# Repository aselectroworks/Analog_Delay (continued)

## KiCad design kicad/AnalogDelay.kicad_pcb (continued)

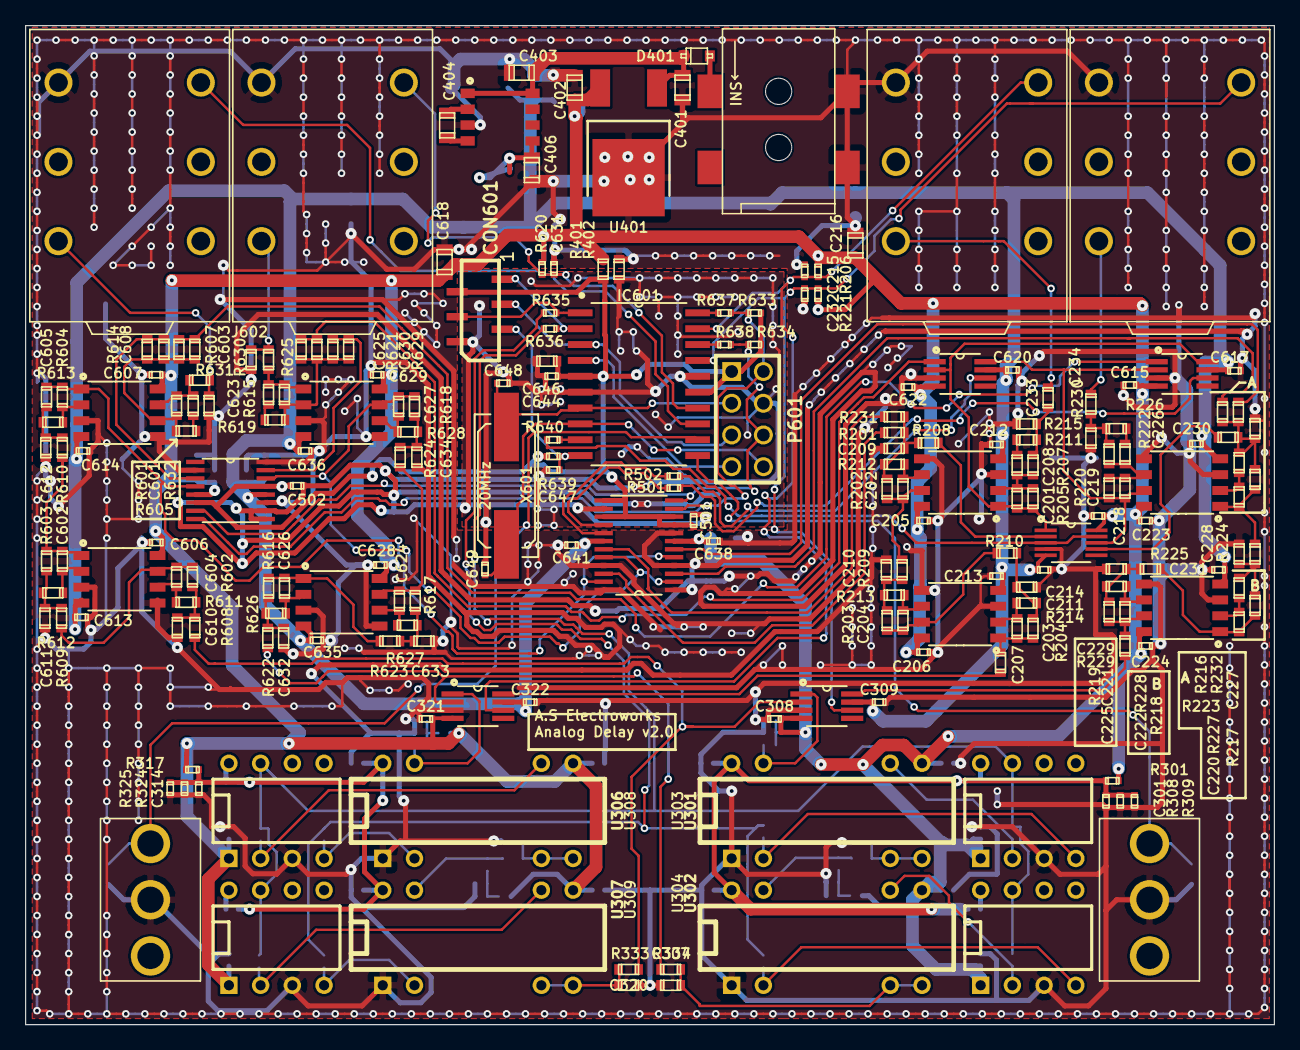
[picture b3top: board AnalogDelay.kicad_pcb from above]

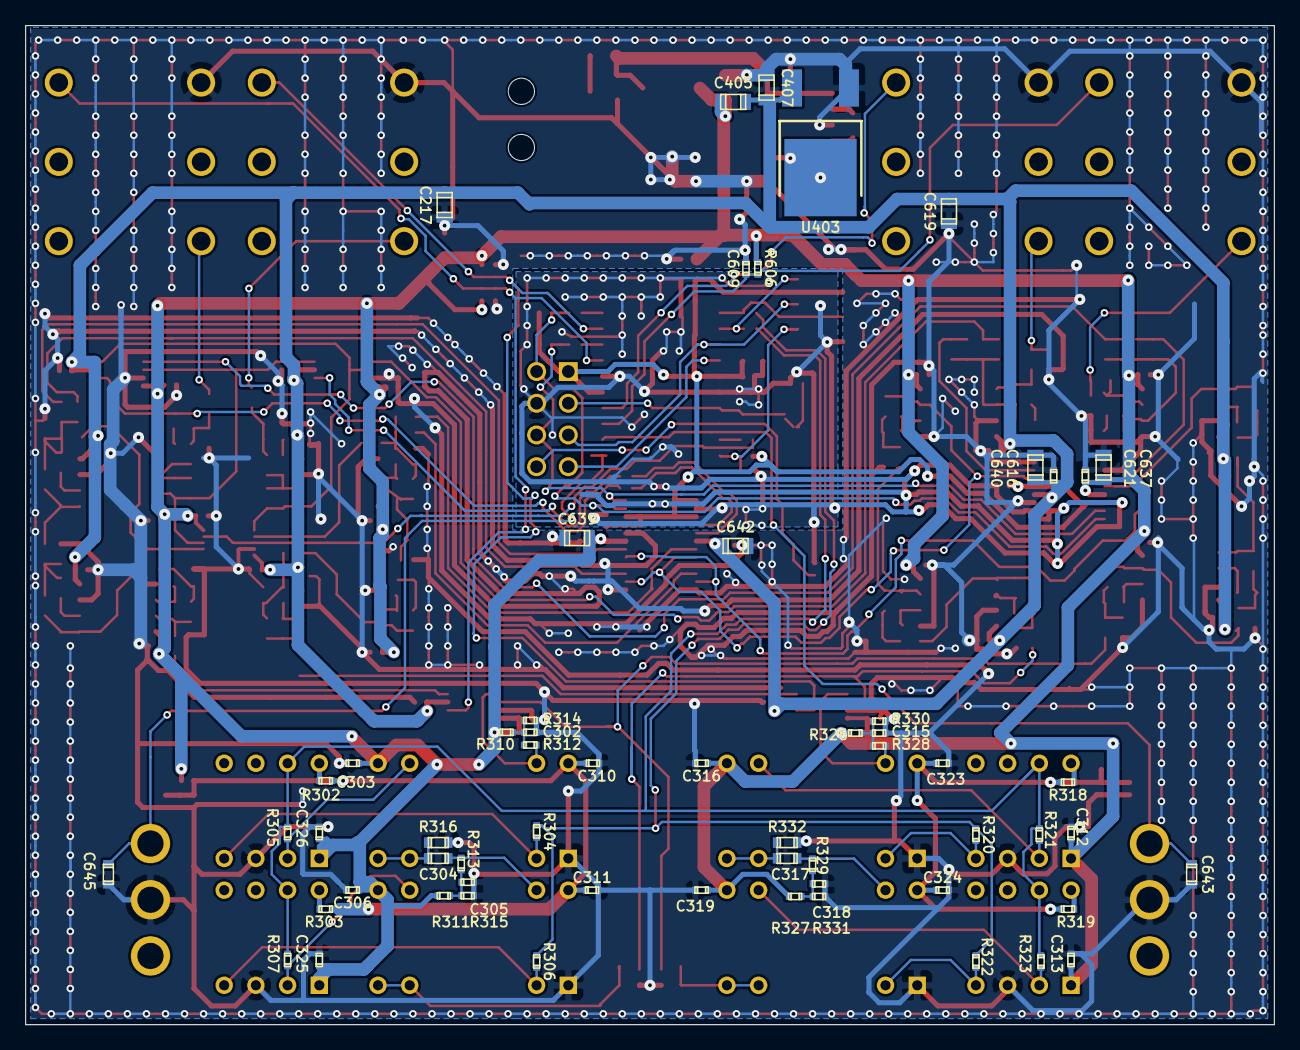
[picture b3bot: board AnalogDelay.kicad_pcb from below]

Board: 4 copper layers, 100.0 x 80.0 mm, 266 parts (59 on the bottom side), 129 nets.

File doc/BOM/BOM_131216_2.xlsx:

ID | Parts Ref. Number | Package | pcs | Value | Toralance | Voltage | Type | Parts Name | Manufacturer | Smart-Prototyping Materials | Shop URL
1 | C631,C609,C635,C613,C628,C606,C213,C206,C218,C214,C321,C205,C212,C615,C616,C617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 | C0402 | 37 | 100n | ±10% | 16V | X7R | GRM155R71C104KA88D | - | Yes | -
2 | R620,R606,R221,R206 | R0402 | 4 | 47k | ±5% | - | - | - | - | Yes | -
3 | R602,R616,R225,R219,R204,R210 | R0603 | 6 | 3.3k | ±5% | - | - | - | - | Yes | -
4 | R611,R626,R229,R214 | R0603 | 4 | 1.5k | ±5% | - | - | - | - | Yes | -
5 | R603,R608,R622,R617 | R0603 | 4 | 2.7k | ±5% | - | - | - | - | Yes | -
6 | R612,R627 | R0603 | 2 | 1.2k | ±5% | - | - | - | - | Yes | -
7 | R609,R623 | R0603 | 2 | 2.2k | ±5% | - | - | - | - | Yes | -
8 | C610,C632,C209,C227 | C0603 | 4 | 22n | ±10% | 25V | X7R | GRM188R71E223KA01D | - | Yes | -
9 | C604,C626,C624,C602,C202,C627,C221,C220,C222,C203,C204,C605 | C0603 | 12 | 10n | ±10% | 25V | X7R | GRM188R71E103KA01D | - | Yes | -
10 | C611,C633,C210,C228 | C0603 | 4 | 33n | ±10% | 16V | X7R | GRM188R71C333KA01D | - | Yes | -
11 | U601,U606,U205,U204,U607,U602,U202,U201 | DMP8 | 8 | NJM4558M | - | - | - | NJM4558M | JRC | - | http://hongkong01.rs-online.com/web/p/operational-amplifiers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
12 | D401 | UMD2 | 1 | 1SS355VMTE-17 | - | - | - | 1SS355VMTE-17 | Rohm | - | http://www.digikey.hk/product-detail/en/1SS355VMTE-17/1SS355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
13 | U403 | DPAK | 1 | MC79M05CDTG | - | - | - | MC79M05CDTG | ON Semiconductor | - | http://www.digikey.hk/product-detail/en/MC79M05CDTG/MC79M05C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
14 | U401 | TO-252-3 | 1 | NJM78M05DL1A | - | - | - | NJM78M05DL1A | JRC | - | http://hongkong02.rs-online.com/web/p/linear-voltage-regulat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
15 | U402 | S8 | 1 | LTC1144CS8 | - | - | - | LTC1144CS8 | Linear Technology | - | http://www.digikey.hk/product-detail/en/LTC1144CS8%23PBF/LTC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
16 | R224,R228,R218,R209,R203,R213 | R0603 | 6 | 3.9k | ±5% | - | - | - | - | Yes | -
17 | R215,R230 | R0603 | 2 | 1M | ±5% | - | - | - | - | Yes | -
18 | R621,R629,R615,R332,R316,R333,R601,R607,R614,R630,R222,R205,R207,R220,R334,R632 | R0603 | 16 | 47k | ±5% | - | - | - | - | Yes | -
19 | R619,R605 | R0603 | 2 | 6.8k | ±5% | - | - | - | - | Yes | -
20 | R402,R401 | R0603 | 2 | 0 | ±5% | - | - | - | - | Yes | -
21 | R604,R618 | R0603 | 2 | 1k | ±5% | - | - | - | - | Yes | -
22 | R613,R610,R624,R628 | R0603 | 4 | 820 | ±5% | - | - | - | - | Yes | -
23 | R625,R631 | R0603 | 2 | 33 | ±5% | - | - | - | - | Yes | -
24 | R226,R211 | R0603 | 2 | 5.1k | ±5% | - | - | - | - | Yes | -
25 | R217,R202,R201,R208,R223,R216,R232,R231 | R0603 | 8 | 5.6k | ±5% | - | - | - | - | Yes | -
26 | R212,R227 | R0603 | 2 | 4.7k | ±5% | - | - | - | - | Yes | -
27 | J401 | MJ-179SMT | 1 | MJ-179SMT | - | - | - | MJ-179SMT | - | - | http://sg.element14.com/multicomp/mj-179smt/chassis-socket-p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
28 | C403,C404,C406,C401,C402,C407,C405,C216,C217,C619,C618,C639,C642,C637,C640 | C0805 | 15 | 10u | ±10% | 10V | X5R | GRM21BR61A106KE19L | - | Yes | -
29 | C208,C623,C226,C601 | C0603 | 4 | 15n | ±10% | 25V | X7R | GRM188R71E153KA01D | - | Yes | -
30 | C634,C612 | C0603 | 2 | 100n | ±10% | 16V | X7R | GRM188R71C104KA01D | - | Yes | -
31 | C630,C625,C603,C608 | C0603 | 4 | 3.3n | ±10% | 50V | X7R | GRM188R71H332KA01D | - | Yes | -
32 | C201,C219 | C0603 | 2 | 1.2n | ±10% | 50V | X7R | GRM188R71H122KA01D | - | Yes | -
33 | C304,C317,C207,C225,C646,C234,C233,C320,C307 | C0603 | 9 | 2.2u | ±10% | 6.3V | X5R | GRM188R60J225KE19D | - | Yes | -
34 | C229,C211 | C0603 | 2 | 82n | ±10% | 16V | X7R | GRM188R71C823KA01D | - | Yes | -
35 | J602,J601,J202,J201 | ACJS-MHDRM | 4 | ACJS-MHDRM | - | - | - | ACJS-MHDRM | Amphenol | - | http://hk.mouser.com/ProductDetail/Amphenol/ACJS-MHDRM/?qs=%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
36 | SW501,SW502 | 8Y10 | 2 | 8Y1021 | - | - | - | 8Y1021 | Fujisoku | - | http://hongkong01.rs-online.com/web/p/push-button-switches/0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
37 | C313,C311,C306,C324,C319,C310,C303,C323,C316,C312,C326,C325 | C0402 | 12 | 1u | ±10% | 10V | X5R | GRM155R61A105KE15D | - | Yes | -
38 | C318,C315,C302,C305 | C0402 | 4 | 10n | ±10% | 50V | X7R | GRM155R71H103KA88D | - | Yes | -
39 | C232,C215 | C0402 | 2 | 1n | ±10% | 50V | X7R | GRM155R71H102KA01D | - | Yes | -
40 | R328,R329,R312,R313 | R0402 | 4 | 100k | ±5% | - | - | - | - | Yes | -
41 | R304,R321,R322,R323,R320,R307,R306,R305 | R0402 | 8 | 0 | ±5% | - | - | - | - | Yes | -
42 | R325,R324,R308,R309 | R0402 | 4 | 12k | ±5% | - | - | - | - | Yes | -
43 | R318,R302,R303,R319 | R0402 | 4 | Don't Source | - | - | - | - | - | - | -
44 | R317,R301 | R0402 | 2 | 5.6k | ±5% | - | - | - | - | Yes | -
45 | R327,R330,R326,R331,R310,R314,R315,R311 | R0402 | 8 | 4.7k | ±5% | - | - | - | - | Yes | -
46 | U608 | RU-16 | 1 | AD5282BRUZ200 | - | - | - | AD5282BRUZ200 | Analog Devices | - | http://www.digikey.hk/product-detail/en/AD5282BRUZ200/AD5282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
47 | R639,R633,R634 | R0402 | 3 | 10k | ±5% | - | - | - | - | Yes | -
48 | R636,R635,R637,R638,R501,R502,R640 | R0402 | 7 | 100 | ±5% | - | - | - | - | Yes | -
49 | X601 | DNP | 1 | Don't Source | - | - | - | - | - | - | -
50 | P601 | DNP | 1 | Don't Source | - | - | - | - | - | - | -
51 | C643,C645 | C0603 | 2 | 1u | ±10% | 10V | X5R | GRM188R61A105KA61D | - | Yes | -
52 | C647 | C0402 | 1 | 1n | ±10% | 50V | X7R | GRM155R71H102KA01D | - | Yes | -
53 | C649,C648 | C0402 | 2 | 22p | ±5% | 50V | C0G | GRM1555C1H220JZ01D | - | Yes | -
54 | IC601 | 20S2 | 1 | ATTINY861A-S | - | - | - | ATTINY861A-S | Atmel | - | http://www.digikey.hk/product-detail/en/ATTINY861A-SUR/ATTIN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
55 | CON601 | 06FMN-BMTTN-A-TF | 1 | 06FMN-BMTTN-A-TF | - | - | - | 06FMN-BMTTN-A-TF | JST | - | http://www.digikey.hk/product-detail/en/06FMN-BMTTN-A-TF(LF)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
56 | U604 | RU-24 | 1 | AD5263BRU200 | - | - | - | AD5263BRU200 | Analog Devices | - | http://www.digikey.hk/product-search/en?WT.z_header=search_g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
57 | U203 | RM-10 | 1 | ADG621BRMZ | - | - | - | ADG621BRMZ | Analog Devices | - | http://www.digikey.hk/product-detail/en/ADG621BRMZ/ADG621BRM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
58 | U605,U603,U310,U305 | RM-8 | 4 | ADG619BRMZ | - | - | - | ADG619BRMZ | Analog Devices | - | http://www.digikey.hk/product-detail/en/ADG619BRMZ/ADG619BRM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
59 | U306,U307,U302,U301 | DNP | 4 | Don't Source | - | - | - | - | - | - | -
60 | U308,U309,U304,U303 | DNP | 4 | Don't Source | - | - | - | - | - | - | -

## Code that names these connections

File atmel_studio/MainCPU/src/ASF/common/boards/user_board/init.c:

/**
 * \file
 *
 * \brief User board initialization template
 *
 */

#include <asf.h>
#include <board.h>
#include <conf_board.h>
#include "ioport.h"

void board_init(void)
{
	/* This function is meant to contain board-specific initialization code
	 * for, e.g., the I/O pins. The initialization can rely on application-
	 * specific board configuration, found in conf_board.h.
	 */
	
	/* I/O Port confuguration */
	ioport_configure_pin(INDET0, IOPORT_DIR_INPUT);
	ioport_configure_pin(INDET1, IOPORT_DIR_INPUT);
	ioport_configure_pin(OUTDET0, IOPORT_DIR_INPUT);
	ioport_configure_pin(OUTDET1, IOPORT_DIR_INPUT);
	ioport_configure_pin(SW0, IOPORT_DIR_INPUT | IOPORT_PULL_UP);
	ioport_configure_pin(SW1, IOPORT_DIR_INPUT | IOPORT_PULL_UP);

	ioport_configure_pin(CLK_N, IOPORT_DIR_OUTPUT | IOPORT_INIT_LOW);
	ioport_configure_pin(CLK_P, IOPORT_DIR_OUTPUT | IOPORT_INIT_HIGH);
	ioport_configure_pin(ENC_A, IOPORT_DIR_INPUT);
	ioport_configure_pin(ENC_B, IOPORT_DIR_INPUT);
	ioport_configure_pin(VOL, IOPORT_DIR_INPUT);
	ioport_configure_pin(FBVOL, IOPORT_DIR_INPUT);
	ioport_configure_pin(ON_OFF, IOPORT_DIR_OUTPUT | IOPORT_INIT_LOW);
	ioport_configure_pin(SCL, IOPORT_DIR_OUTPUT | IOPORT_INIT_HIGH);
	ioport_configure_pin(SDA, IOPORT_DIR_OUTPUT | IOPORT_INIT_HIGH);
	
		
}

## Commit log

2014-06-07 1st Commit
2014-06-07 Add: Library cache.lib(kicad)
2014-06-07 Add: compander sch&pcb mod: constants
2014-06-08 Create gh-pages branch via GitHub
2014-06-15 mod: Schematics
2014-06-15 Fix: IN2 NOT Enable
2015-02-14 Mod: Delay Mode Type(Add dotted sixteen note, triplet eighth mode, remove dotted quarter note). Mod: Delay Mode Icons.
